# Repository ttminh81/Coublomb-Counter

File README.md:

A circuit implement the usage of BQ35100 Lithium Primary Battery Fuel Gauge.

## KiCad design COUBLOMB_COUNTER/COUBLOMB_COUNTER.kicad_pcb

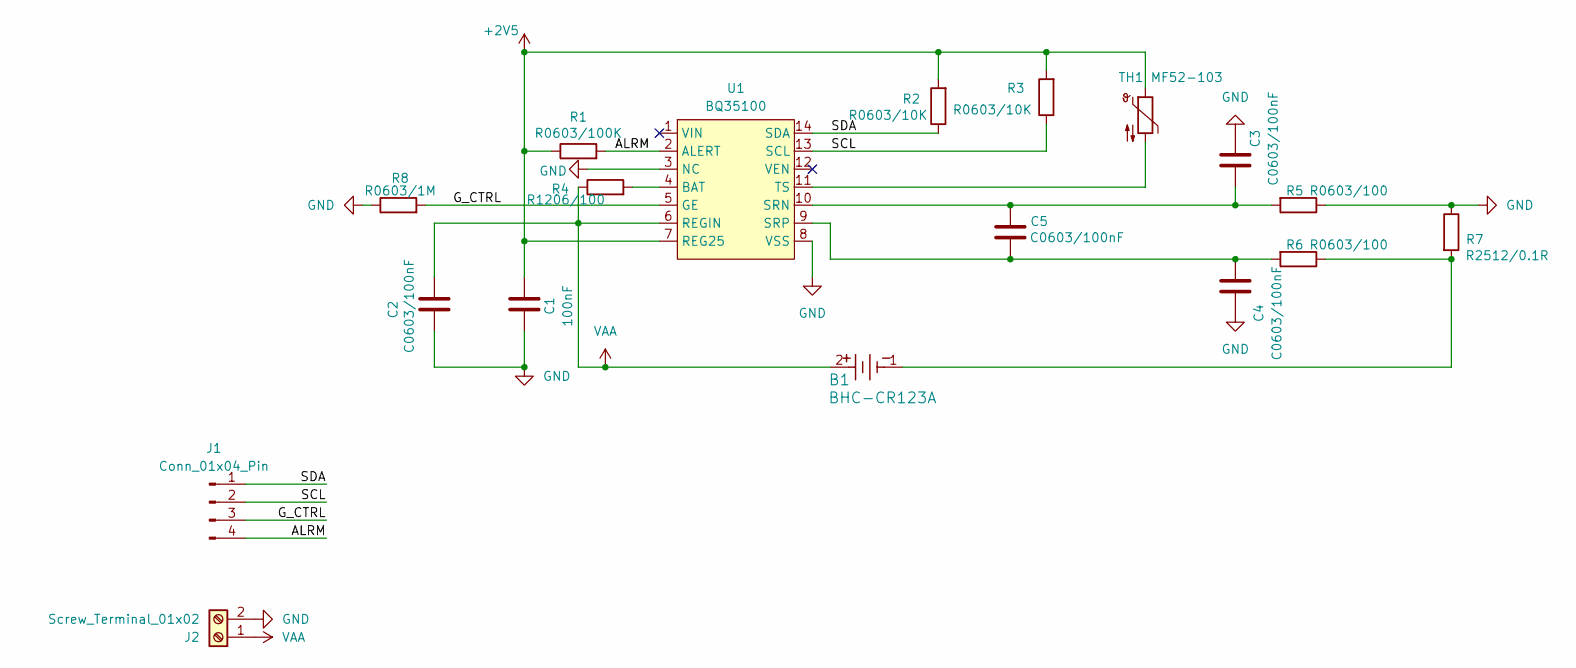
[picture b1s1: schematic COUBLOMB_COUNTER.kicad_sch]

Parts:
B1: BHC-CR123A; BHC-CR123A_PPW
C1: 100nF; C_0603_1608Metric
C2, C3, C4, C5: C0603/100nF; C_0603_1608Metric
J1: Conn_01x04_Pin; PinHeader_1x04_P2.54mm_Vertical
J2: Screw_Terminal_01x02; TerminalBlock_4Ucon_1x02_P3.50mm_Horizontal
R1: R0603/100K; R0603_HandSoldering
R2, R3: R0603/10K; R0603_HandSoldering
R4: R1206/100; R_1206_3216Metric
R5, R6: R0603/100; R0603_HandSoldering
R7: R2512/0.1R; R_2512_6332Metric
R8: R0603/1M; R0603_HandSoldering
TH1: MF52-103
U1: BQ35100; TSSOP-14_4.4x5mm_P0.65mm

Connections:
+2V5: C1.2, R1.1, R2.2, R3.2, TH1.1, U1.7 (REG25)
/ALRM: J1.4, R1.2, U1.2 (ALERT)
/G_CTRL: J1.3, R8.2, U1.5 (GE)
/SCL: J1.2, R3.1, U1.13 (SCL)
/SDA: J1.1, R2.1, U1.14 (SDA)
GND: C1.1, C2.1, C3.2, C4.1, J2.2, R5.1, R7.1, R8.1, U1.3 (NC), U1.8 (VSS)
unnamed: B1.1, R6.1, R7.2
unnamed: R4.2, U1.4 (BAT)
unnamed: C3.1, C5.2, R5.2, U1.10 (SRN)
unnamed: C4.2, C5.1, R6.2, U1.9 (SRP)
unnamed: TH1.2, U1.11 (TS)
VAA: B1.2, C2.2, J2.1, R4.1, U1.6 (REGIN)

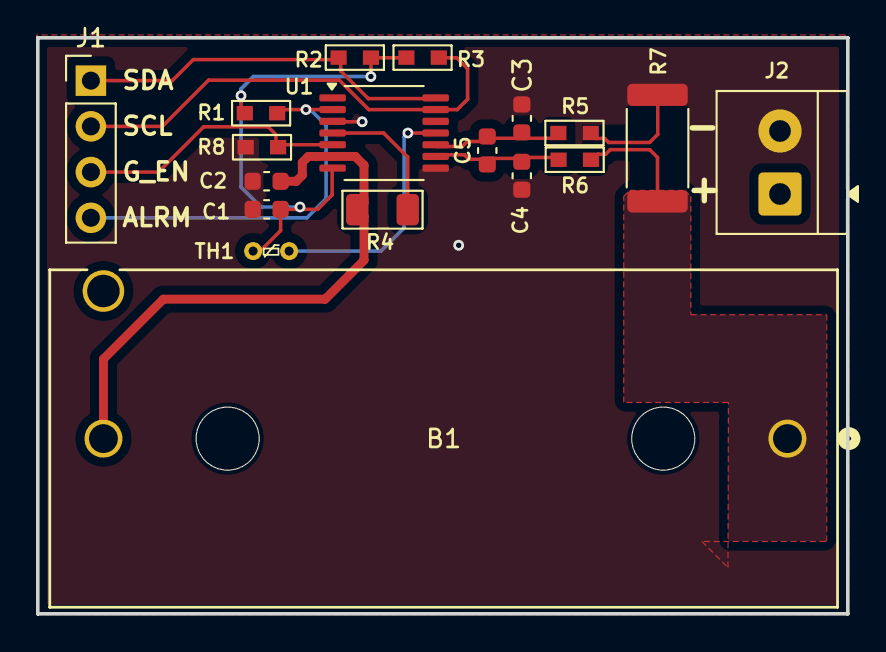
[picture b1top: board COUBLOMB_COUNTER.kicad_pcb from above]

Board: 2 copper layers, 45.0 x 32.0 mm, 18 parts (0 on the bottom side), 12 nets.

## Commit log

2025-11-06 Add schematic and PCB
